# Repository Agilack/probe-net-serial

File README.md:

# probe-net-serial
Ethernet to serial adapter. Allow remote control of a serial port (remote console, debug port, ...) 

 * hw-netserial-r01: Hardware board

 * sw-bootloader: Allow flash/update using DHCP and TFTP (if SW0 is pushed on startup)

 * sw-unit_tests: Some unit-tests for software and hardware

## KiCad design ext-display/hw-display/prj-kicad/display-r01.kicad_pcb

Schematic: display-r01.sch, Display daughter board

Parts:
C101, C102, C109, C110: 1uF
C103, C105: 10uF
C106, C108: 4,7uF
C107: 2,2uF
C111: C
DISP1: ER-OLED0.91-1
DISP2: ER-OLED0.91-3
L101: 4.7uH
MISO1: CONN_1
P1, P2, P3: CONN_1
PP1, PP2: CONN_1
R101, R102: R
R103: 560k
TP101, TP102, TP103: CONN_1
U1: EFM8BB10F8G-A-SOIC16
U2: TLV61220

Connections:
+3.3V: C105.1, DISP1.7 (VDD), DISP2.7 (VDD), L101.1, P1.1, U1.5, U2.3 (EN), U2.6 (VBAT)
DISP_DC: DISP1.10 (D/C), DISP2.10 (D/C), U1.11 (P1.0)
DISP_RST: DISP1.9 (RES), DISP2.9 (RES), U1.10 (P1.1)
GND: C103.2, C105.2, C106.2, C107.2, C108.2, C111.2, DISP1.6, DISP2.6, P2.1, R102.2, R103.2, U1.4, U2.2
IREF: DISP1.13 (IREF), DISP2.13 (IREF), R103.1
unnamed: R101.2, R102.1, U2.4 (FB)
unnamed: MISO1.1, U1.2 (P0.1)
unnamed: TP101.1, U1.15 (P0.4)
unnamed: C101.2, DISP1.4 (C1N)
unnamed: C111.1, DISP2.14 (VCOMH)
unnamed: C108.1, DISP2.15 (VCC)
unnamed: C101.1, DISP1.3 (C1P)
unnamed: C102.1, DISP1.1 (C2P)
unnamed: C102.2, DISP1.2 (C2N)
unnamed: L101.2, U2.1 (SW)
unnamed: PP1.1, U1.7 (P2.0)
unnamed: PP2.1, U1.6 (RST)
unnamed: C106.1, DISP1.15 (VCC)
unnamed: C107.1, DISP1.14 (VCOMH)
unnamed: C110.1, DISP2.1 (C2P)
unnamed: TP102.1, U1.13 (P0.6)
unnamed: TP103.1, U1.12 (P0.7)
unnamed: C109.2, DISP2.4 (C1N)
unnamed: C109.1, DISP2.3 (C1P)
unnamed: C110.2, DISP2.2 (C2N)
SPI_CS: DISP1.8 (CS), DISP2.8 (CS), U1.16 (P0.3)
SPI_MOSI: DISP1.12 (SDIN), DISP2.12 (SDIN), U1.1 (P0.2)
SPI_SCK: DISP1.11 (SCLK), DISP2.11 (SCLK), U1.3 (P0.0)
UART_RX: P3.1, U1.14 (P0.5)

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
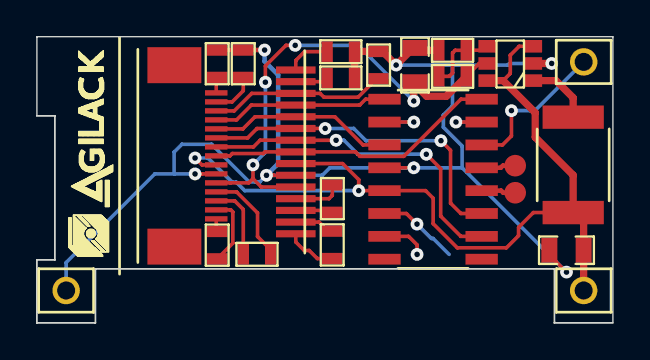
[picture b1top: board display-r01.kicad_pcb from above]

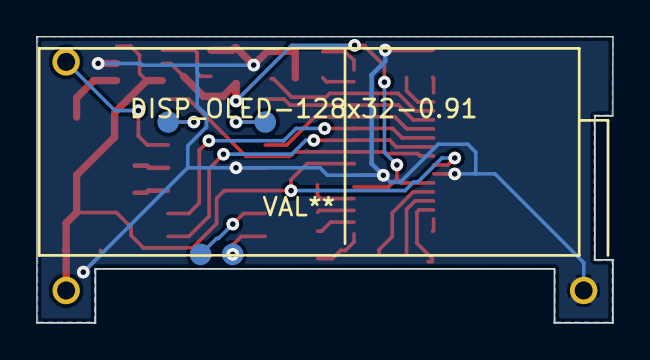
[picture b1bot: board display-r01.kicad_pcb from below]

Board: 2 copper layers, 32.0 x 15.9 mm, 29 parts (5 on the bottom side), 30 nets.

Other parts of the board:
DISP_OLED-128x32-0.91: VAL**; DISP_OLED-128x32-0.91-1-rev
agilack-11.5: 450px; agilack-11.5

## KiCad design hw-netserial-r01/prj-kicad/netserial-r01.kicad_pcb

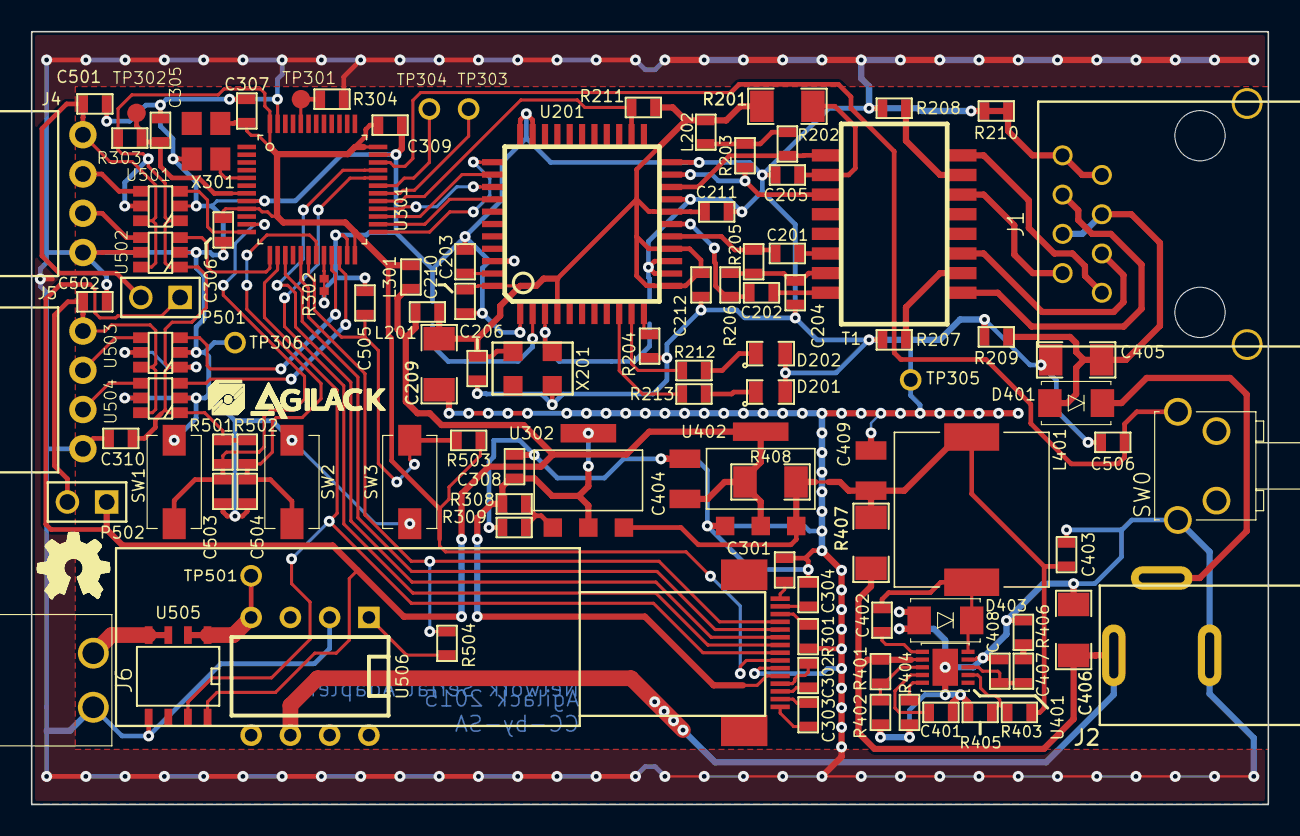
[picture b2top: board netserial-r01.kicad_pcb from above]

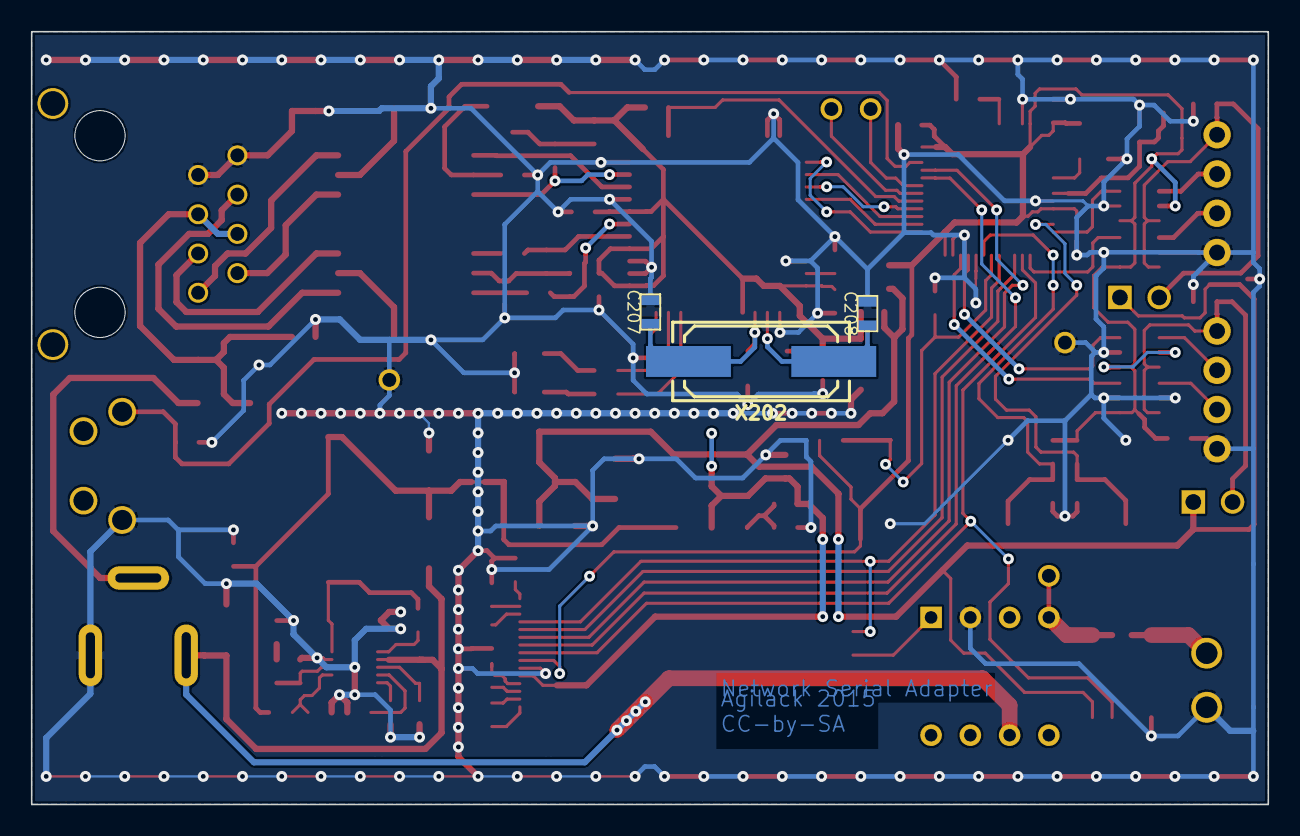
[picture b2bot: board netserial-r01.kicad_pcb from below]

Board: 2 copper layers, 80.0 x 50.0 mm, 113 parts (3 on the bottom side), 80 nets.

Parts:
C201, C202: 68nF; SMD0603
C203, C308: 10uF; SMD0603
C204, C205, C401: 10nF; SMD0603
C206, C210, C211, C212, C305, C306, C307, C309, C310, C501, C502, C503, C504, C505, C506: C; SMD0603
C207, C208: 18pF; SMD0603
C209: 2,2uF; SMD1206
C301: 4,7uF; SMD0603
C302, C303, C403: 1uF; SMD0603
C304: 2,2uF; SMD0603
C402: 100nF; SMD0603
C404, C409: 47uF; C_TAJB
C405, C406: 10uF; SMD1206
C407: 180pF; SMD0603
C408: 10Pf; SMD0603
D201, D202: LED; SMD0805p
D401: S1D; DO214-AC
D403: B160; DO214-AC
DISP1: ER-OLED0.91-3; CONN_ER-CON15HT-1
DISP_OLED-128x32-0.91: VAL**; DISP_OLED-128x32-0.91
J1: CONN_RJ45; CONN_615008140121
J2: DC10A-2.1; CONN_DC-10
J4, J5: CONN_4; CONN_BG302-04
J6: CONN_2; CONN_691322110002
L201: INDUCTOR; SMD0603
L202, L301: FB100; SMD0603
L401: 47uH; I_MSS1048
P501, P502: JUMPER; CONN_2
R201: 10; SMD1206
R202, R203, R205, R206: 49.9; SMD0603
R204: 12.4k; SMD0603
R207, R208, R209: 75; SMD0603
R210, R308, R309, R403, R405, R504: R; SMD0603
R211, R401, R404: 100k; SMD0603
R212, R213: 330; SMD0603
R301: 560k; SMD0603
R302: 0; SMD0402
R303, R304, R501, R502, R503: 10k; SMD0603
R402: 48.7k; SMD0603
R406: 75K; SMD0603
R407, R408: 0; SMD1206
SW0: SW_PUSH; SW_SKHHLRA010
SW1, SW2, SW3: SW_PUSH; SW_434123043816
T1: TRANSFORMER_1:1; TR_W749013011
TP301, TP302: CONN_1; TP_SMD
TP303, TP304, TP305, TP306, TP501: CONN_1; TP_PIN
U201: ENC424J600; TQFP44
U301: STM32F103CX; LQFP48
U302: LDO_1117-ADJ; SOT223
U401: TPS54060; SMD_SON10
U402: LDO_1117-3.3; SOT223
U501, U502, U503, U504: SN74LVC1T45; SOT23-6
U505: ACS711; SMD_SO8E
U506: VO14642AT; DIP-8__300
X201: 25MHz; Q_HC536
X202: 25MHz; Q_49U3HMS
X301: 7.3728MHz; Q_3.2x2.5
agilack-11.5: 450px; agilack-11.5
ohw_logo: VAL**; ohw-logo

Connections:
+3.3V: C404.1, L201.1, L301.1, P501.1, P502.1, R408.2, U402.2, U402.4, U505.8
+5V: C403.1, C409.1, L401.2, R403.1, R407.2, R408.1, U302.3, U402.3
+Vcpu: C306.1, C307.1, C309.1, C310.1, DISP1.7, L301.2, R303.1, R501.1, R502.1, R503.1, U301.9, U301.24, U301.36, U301.48, U501.1, U501.5, U502.1, U503.1, U503.5, U504.1, X301.4
+Veth: C206.1, C209.1, C210.1, C211.1, C212.1, L201.2, L202.2, R201.1, R211.1, U201.4, U201.12, U201.15, U201.18, U201.44, X201.4
+Vin: C406.1, J2.2, R401.1, R407.1, U401.2, U506.6
+Vpoe: C405.1, D401.1, J1.4, J1.5, R209.2
+Vport1: C501.1, J4.4, P501.2, U501.6, U502.6
+Vport2: C502.1, J5.4, P502.2, U503.6, U504.6
Boot0: R304.1, TP301.1, U301.44
DISP_CD: DISP1.10, U301.33
DISP_RST: DISP1.9, U301.32
ETH_IT: R211.2, U201.24, U301.29
GND: C203.2, C204.2, C205.2, C206.2, C207.2, C208.2, C209.2, C210.2, C211.2, C212.2, C301.2, C304.2, C305.2, C306.2, C307.2, C308.2, C309.2, C310.2, C401.2, C403.2, C404.2, C405.2, C406.2, C408.2, C409.2, C501.2, C502.2, C503.2, C504.2, C505.2, C506.2, D201.2, D202.2, D403.1, DISP1.6, J1.7, J1.8, J2.1, J4.1, J5.1, J6.2, R204.2, R207.1, R208.2, R209.1, R210.1, R210.2, R301.2, R302.1, R302.2, R304.2, R309.2, R402.2, R404.2, R405.2, R406.2, SW0.1, SW1.1, SW2.1, SW3.1, TP305.1, TP306.1, U201.1, U201.13, U201.14, U201.19, U201.22, U201.32, U201.33, U201.42, U301.8, U301.20, U301.23, U301.35, U301.47, U401.9, U401.PAD, U402.1, U501.2, U502.2, U502.5, U503.2, U504.2, U504.5, U505.5, U506.2, X201.2, X301.2
unnamed: C207.1, U201.3, X201.3, X202.1
unnamed: C208.1, U201.2, X202.2
unnamed: R213.2, U201.9
unnamed: R212.1, U201.10
unnamed: D201.1, R213.1
unnamed: D202.1, R212.2
unnamed: R208.1, T1.15
unnamed: J1.2, T1.14
unnamed: J1.1, T1.16
unnamed: J1.3, T1.11
unnamed: J1.6, T1.9
unnamed: C201.2, T1.6
unnamed: R207.2, T1.10
unnamed: C202.2, T1.8
unnamed: R202.1, T1.1, U201.20
unnamed: C203.1, U201.43
unnamed: R204.1, U201.11
unnamed: R203.2, T1.3, U201.21
unnamed: L202.1, R202.2, R203.1
unnamed: C205.1, R201.2, T1.2
unnamed: C204.1, R205.1, R206.2, T1.7
unnamed: C201.1, R205.2, U201.16
unnamed: C202.1, R206.1, U201.17
unnamed: C308.1, DISP1.5, R308.1, U302.2, U302.4
unnamed: R308.2, R309.1, U302.1
unnamed: U301.5, X301.3
unnamed: C303.1, DISP1.1
unnamed: C304.1, DISP1.14
unnamed: C303.2, DISP1.2
unnamed: C302.2, DISP1.4
unnamed: C302.1, DISP1.3
unnamed: C301.1, DISP1.15
unnamed: DISP1.13, R301.1
unnamed: R403.2, R405.1, U401.7
unnamed: C407.1, C408.1, U401.8
unnamed: C407.2, R406.1
unnamed: C402.1, U401.1
unnamed: R401.2, R402.1, U401.3
unnamed: C402.2, D403.2, L401.1, U401.10
unnamed: C401.1, U401.4
unnamed: R404.1, U401.5
unnamed: D401.2, J2.3
unnamed: R504.2, U506.1
unnamed: J6.1, U505.3, U505.4
unnamed: TP501.1, U505.1, U505.2, U506.4
unnamed: J4.3, U501.4
unnamed: J5.3, U503.4
unnamed: J4.2, U502.4
unnamed: J5.2, U504.4
PWR_SENSE: DISP1.8, U301.14, U505.7
Reset: C305.1, R303.2, TP302.1, U301.7
SPI1_MOSI: DISP1.12, R504.1, U301.17
SPI1_SCK: DISP1.11, U301.15
SPI2_MISO: U201.35, U301.27
SPI2_MOSI: U201.36, U301.28
SPI2_NSS: U201.34, U301.25
SPI2_SCK: U201.37, U301.26
SW0: C506.1, SW0.2, U301.34
SW1: C503.1, R501.2, SW1.2, U301.11
SW2: C504.1, R502.2, SW2.2, U301.19
SW3: C505.1, R503.2, SW3.2, U301.18
UART2_RX: U301.13, U502.3
UART2_TX: U301.12, U501.3
UART3_RX: U301.22, U504.3
UART3_TX: U301.21, U503.3
UART_RX: TP304.1, U301.31
UART_TX: TP303.1, U301.30

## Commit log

2015-03-23 = ADD: Unit test software for ethernet interface
2015-03-24 = ADD: Unit test software, uIP stack with ethernet interface
2015-03-25 = UPD: Fix ethernet ut bug when TX is used without hardware interrupt
2015-04-20 = ADD: bootloader, allow reflash using dhcp/tftp
2015-04-21 = ADD: Unit Test for bootloader : "Hello World"
2015-04-22 = ADD: Unit test for OLED display
2015-04-23 = UPD: Improve loader/firmware integration - Start external oscillator and PLL before calling firmware - Add API vectors entry - uart functions
2015-05-27 = UPD: Optimize SPI functions - Remove function pointers (reduce code size, and increase speed) - Update ethernet ENC driver
2015-05-28 = UPD: Fix ethernet issues - Fix ARP init bug (bad cache index) - Init MAC address on init, and move it from ip to eth layer - Remove old/unused dhcp callback
2015-05-28 = UPD: Improve network services (dhcp, tftp) - Move DHCP call from eth layer to app layer - Move TFTP call from dhcp layer to app layer
2015-05-29 = UPD: Improve boot - Test if the firmware image is valid before jumping to it - Relocate vectors to allow firmware to get interrupts - Use systick instead of timer2
2015-05-29 = ADD: Create a dedicated file for time functions - Now the system time is based on systick
2015-06-01 = UPD: Improve network layer - Remove fixed rx/tx buffers and create dynamic position functions - Add an extensible protocol support to allow, for example TCP suport into fw - Reduce the needed RAM t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
2015-06-01 = FIX: Improve IP datagram - Compute ip length into ip_tx() - Fix fragment offset bug (sometimes uninitialized) - Add network function to API / link space
2015-06-02 = ADD: Telnet server using bootloader network API
2015-06-03 = ADD: Unit test for UART2 and UART3
2015-06-03 = UPD: Add DMA support - Create uartX_putm functions to send datas using DMA - Init channels and buffers for RX - Add a generic memory-to-memory copy function
2015-06-04 = UPD: Improve ethernet TX - Change SPI prescaler -> clk/2 - Use one WCRU transaction instead of 4 WCR to set TX addr and TX len - Use dedicated SBI to start TX - Remove bank sel when SFR are availab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
2015-06-05 = ADD: First revision of the netserial PCB board
2015-06-09 = ADD: Gerber and production files for netserial PCB
2015-06-18 = UPD: Move all unit-tests to a dedicated folder
2015-06-29 = Create a new branch for (old) rev01
2015-06-29 = UPD: Fix info files
2015-06-29 = UPD: Fix info file
2015-06-30 = ADD: Create extension board for display
2015-07-01 = ADD: Generate production files for display extension board
2015-07-02 = ADD: Software unit-test for display MCU (8051)
2015-07-07 = ADD: Software unit-tests for display extension - UT UART
2015-07-07 = ADD: New unit-test for display extension, UT OLED (show image)
2015-07-08 = ADD: Default firmware for display extension, with character generator
2015-07-08 = FIX: change UART speed to improve 115200 communication
2015-07-09 = UPD: Improve character generator (increase SPI speed and reduce CS time lost)
2015-07-12 = UPD: Add a display function to select the current line (0 to 3)
2015-07-16 = UPD: Add support of 32x32 icon load at the begining of line - Icon are sent as raw data, encoded in hexadecimal ascii chars - When an icon is displayed, an offset is added to text

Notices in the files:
hw-netserial-r01/prj-kicad/netserial-r01.kicad_pcb:
CC-by-SA
